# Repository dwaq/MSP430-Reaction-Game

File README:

MSP430-Reaction-Game
====================

The object of the game is to stop the cycling LEDs at a specific LED to test your reaction skills. The TI MSP430G2231 microcontroller drives 8 LEDs via 3 pins using a 74HC595 shift register. The speed that the LEDs flash is determined from the potentiometer wiper via the analog to digital converter in the MSP430. There are also 2 pushbuttons to start/restart and stop the game. Everything is powered from a 9V battery that is dropped down to 3.3V via a LD1117V33 voltage regulator. There is also a programming header to program the microcontroller in-circuit with a TI Launchpad.

Read the full details on my blog at http://tinkeringetc.blogspot.com/p/msp430-reaction-game.html

This work is licensed under a Creative Commons Attribution 3.0 Unported License.

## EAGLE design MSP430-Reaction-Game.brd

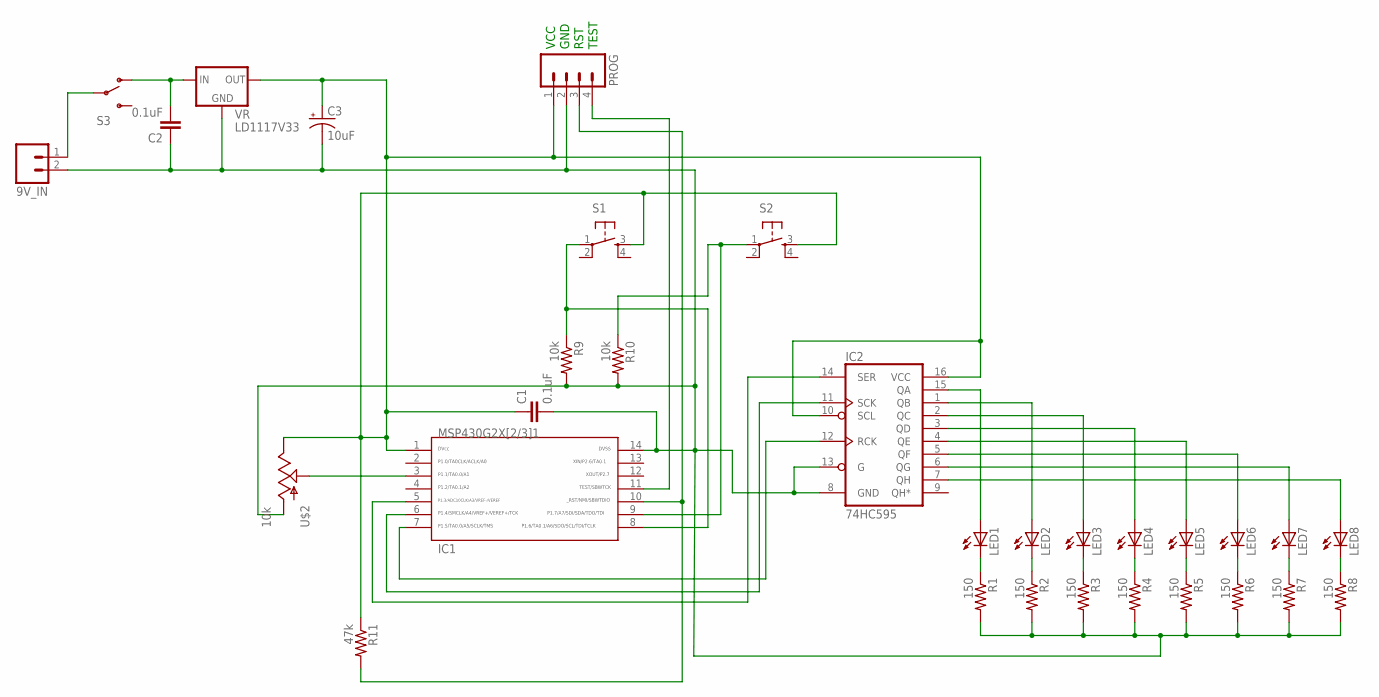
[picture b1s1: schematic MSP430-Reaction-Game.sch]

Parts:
9V_IN: M02PTH3; 1X02_LONGPADS
C1, C2: 0.1uF; CAP-PTH-SMALL2
C3: 10uF; CPOL-RADIAL-100UF-25V
IC1: MSP430G2231; N14
IC2: 74HC595; DIL16
LED1, LED2, LED3, LED4, LED5, LED6, LED7, LED8: LED5MM
PROG: M04LOCK; 1X04_LOCK
R1, R2, R3, R4, R5, R6, R7, R8: 150; 0207/10
R9, R10: 10k; 0207/10
R11: 47k; 0207/10
S1, S2: TAC_SWITCHPTH; TACTILE-PTH
S3: SWITCH-SPSTKIT; SWITCH-SPDT_KIT
U$2: 10k; ALPS_POT
VR: LD1117V33; 78XXL

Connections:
unnamed: LED1.K (C), R1.1
unnamed: LED2.K (C), R2.1
unnamed: LED3.K (C), R3.1
unnamed: LED4.K (C), R4.1
unnamed: LED5.K (C), R5.1
unnamed: LED6.K (C), R6.1
unnamed: LED7.K (C), R7.1
unnamed: LED8.K (C), R8.1
unnamed: IC2.15 (QA), LED1.A
unnamed: IC2.1 (QB), LED2.A
unnamed: IC2.2 (QC), LED3.A
unnamed: IC2.3 (QD), LED4.A
unnamed: IC2.4 (QE), LED5.A
unnamed: IC2.5 (QF), LED6.A
unnamed: IC2.6 (QG), LED7.A
unnamed: IC2.7 (QH), LED8.A
unnamed: C1.1, C3.1 (+), IC1.1, IC2.10 (SCL), IC2.16 (VCC), PROG.1, R11.1, S1.3, S2.3, U$2.P$1 (E), VR.GND (OUT)
unnamed: IC1.10, PROG.3, R11.2
unnamed: IC1.3, U$2.P$2 (S)
unnamed: IC1.5, IC2.14 (SER)
unnamed: IC1.7, IC2.12 (RCK)
unnamed: IC1.6, IC2.11 (SCK)
unnamed: IC1.8, R9.1, S1.1
unnamed: IC1.9, R10.1, S2.1
unnamed: 9V_IN.2, C1.2, C2.1, C3.2 (-), IC1.14, IC2.8 (GND), IC2.13 (G), PROG.2, R1.2, R2.2, R3.2, R4.2, R5.2, R6.2, R7.2, R8.2, R9.2, R10.2, U$2.P$3 (A), VR.IN (GND)
unnamed: IC1.11, PROG.4
unnamed: 9V_IN.1, S3.2
unnamed: C2.2, S3.1 (O), VR.OUT (IN)

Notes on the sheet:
VCC
GND
RST
TEST

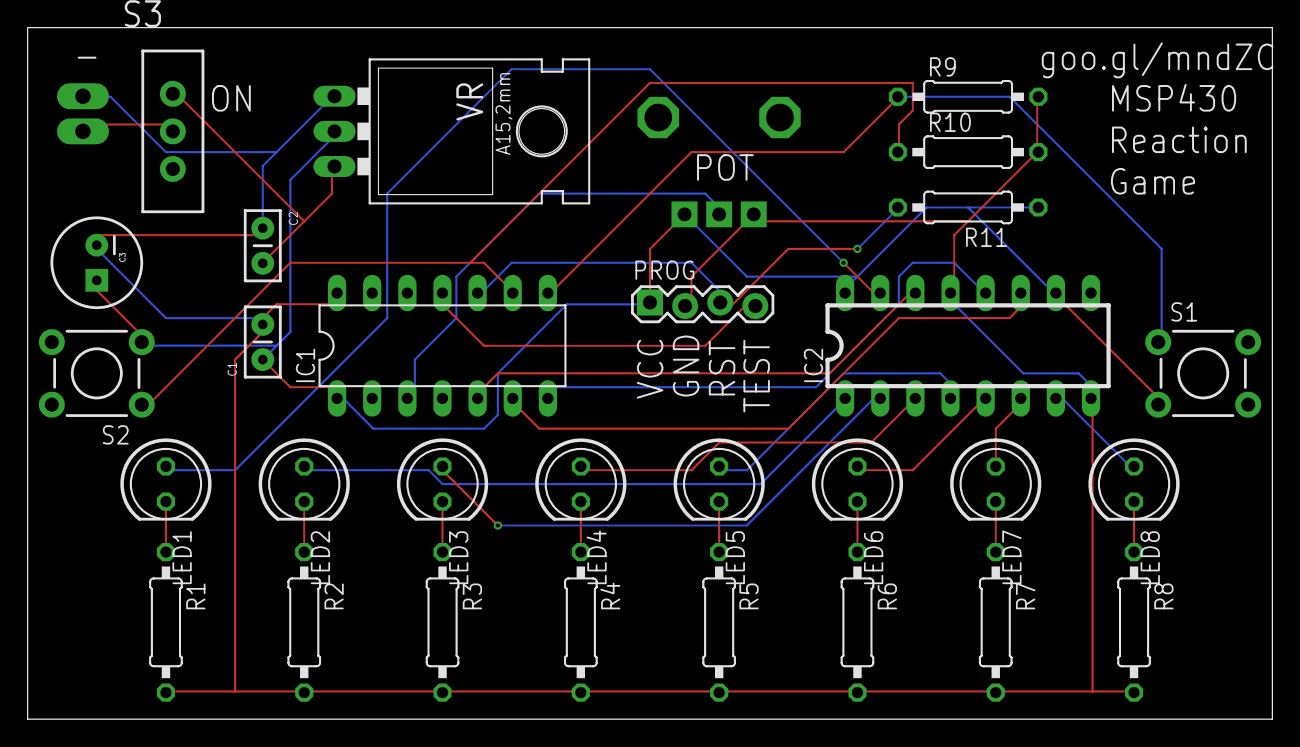
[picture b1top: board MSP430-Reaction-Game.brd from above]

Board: 2 copper layers, 90.0 x 50.0 mm, 31 parts (0 on the bottom side), 28 nets.

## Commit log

2012-01-18 removed some files to rename later on
2012-01-18 Eagle files sent to manufacture
2012-02-08 Gerber board files sent for manufacture
2012-02-08 Switched buttons around in code to match what is on the PCB
2012-02-14 Final details about the project"
2012-03-04 updated licensing information
2012-05-09 can now restart after game with same speed or different speed
2012-05-16 Modified formatting
2012-05-16 added formatting
2012-05-16 removed old README
2012-06-12 images of eagle files - 600 dpi
2012-08-15 Added license info to code

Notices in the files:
parts and their libraries:
SparkFun: Licensing: CC v3.0 Share-Alike You are welcome to use this library for commercial purposes.
